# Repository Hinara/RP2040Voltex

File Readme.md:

# RP2040Voltex

Work in progress !! The PCB nor the schematics have been tested for now !! It is just a proof of concept !

It is a mini controller for games such as Sound Voltex, and clones.

This model is based on [Pocket-SDVX-Pico](https://github.com/speedypotato/Pocket-SDVX-Pico-v4)
The Lower PCB should be compatible [Pocket-SDVX-Pico](https://github.com/speedypotato/Pocket-SDVX-Pico-v4)

It's main difference is using directly a RP2040 processor to be able to meet the height constraints on the upper face. This was designed like that to prevent ripping of some Pico's component while putting the Pocket SDVX Pico in a bag without a case.

## Firmware

For now the firmware as not been updated to math the RP2040 pin layout, but you should be able to have a working firmware by compiling the [Pocket-SDVX-Pico](https://github.com/speedypotato/Pico-Game-Controller) firmware and change the pin layout.

## License

As it is derived work from [Pocket-SDVX-Pico](https://github.com/speedypotato/Pocket-SDVX-Pico-v4) it inherits the same [license](https://github.com/speedypotato/Pocket-SDVX-Pico-v4/blob/main/LICENSE).

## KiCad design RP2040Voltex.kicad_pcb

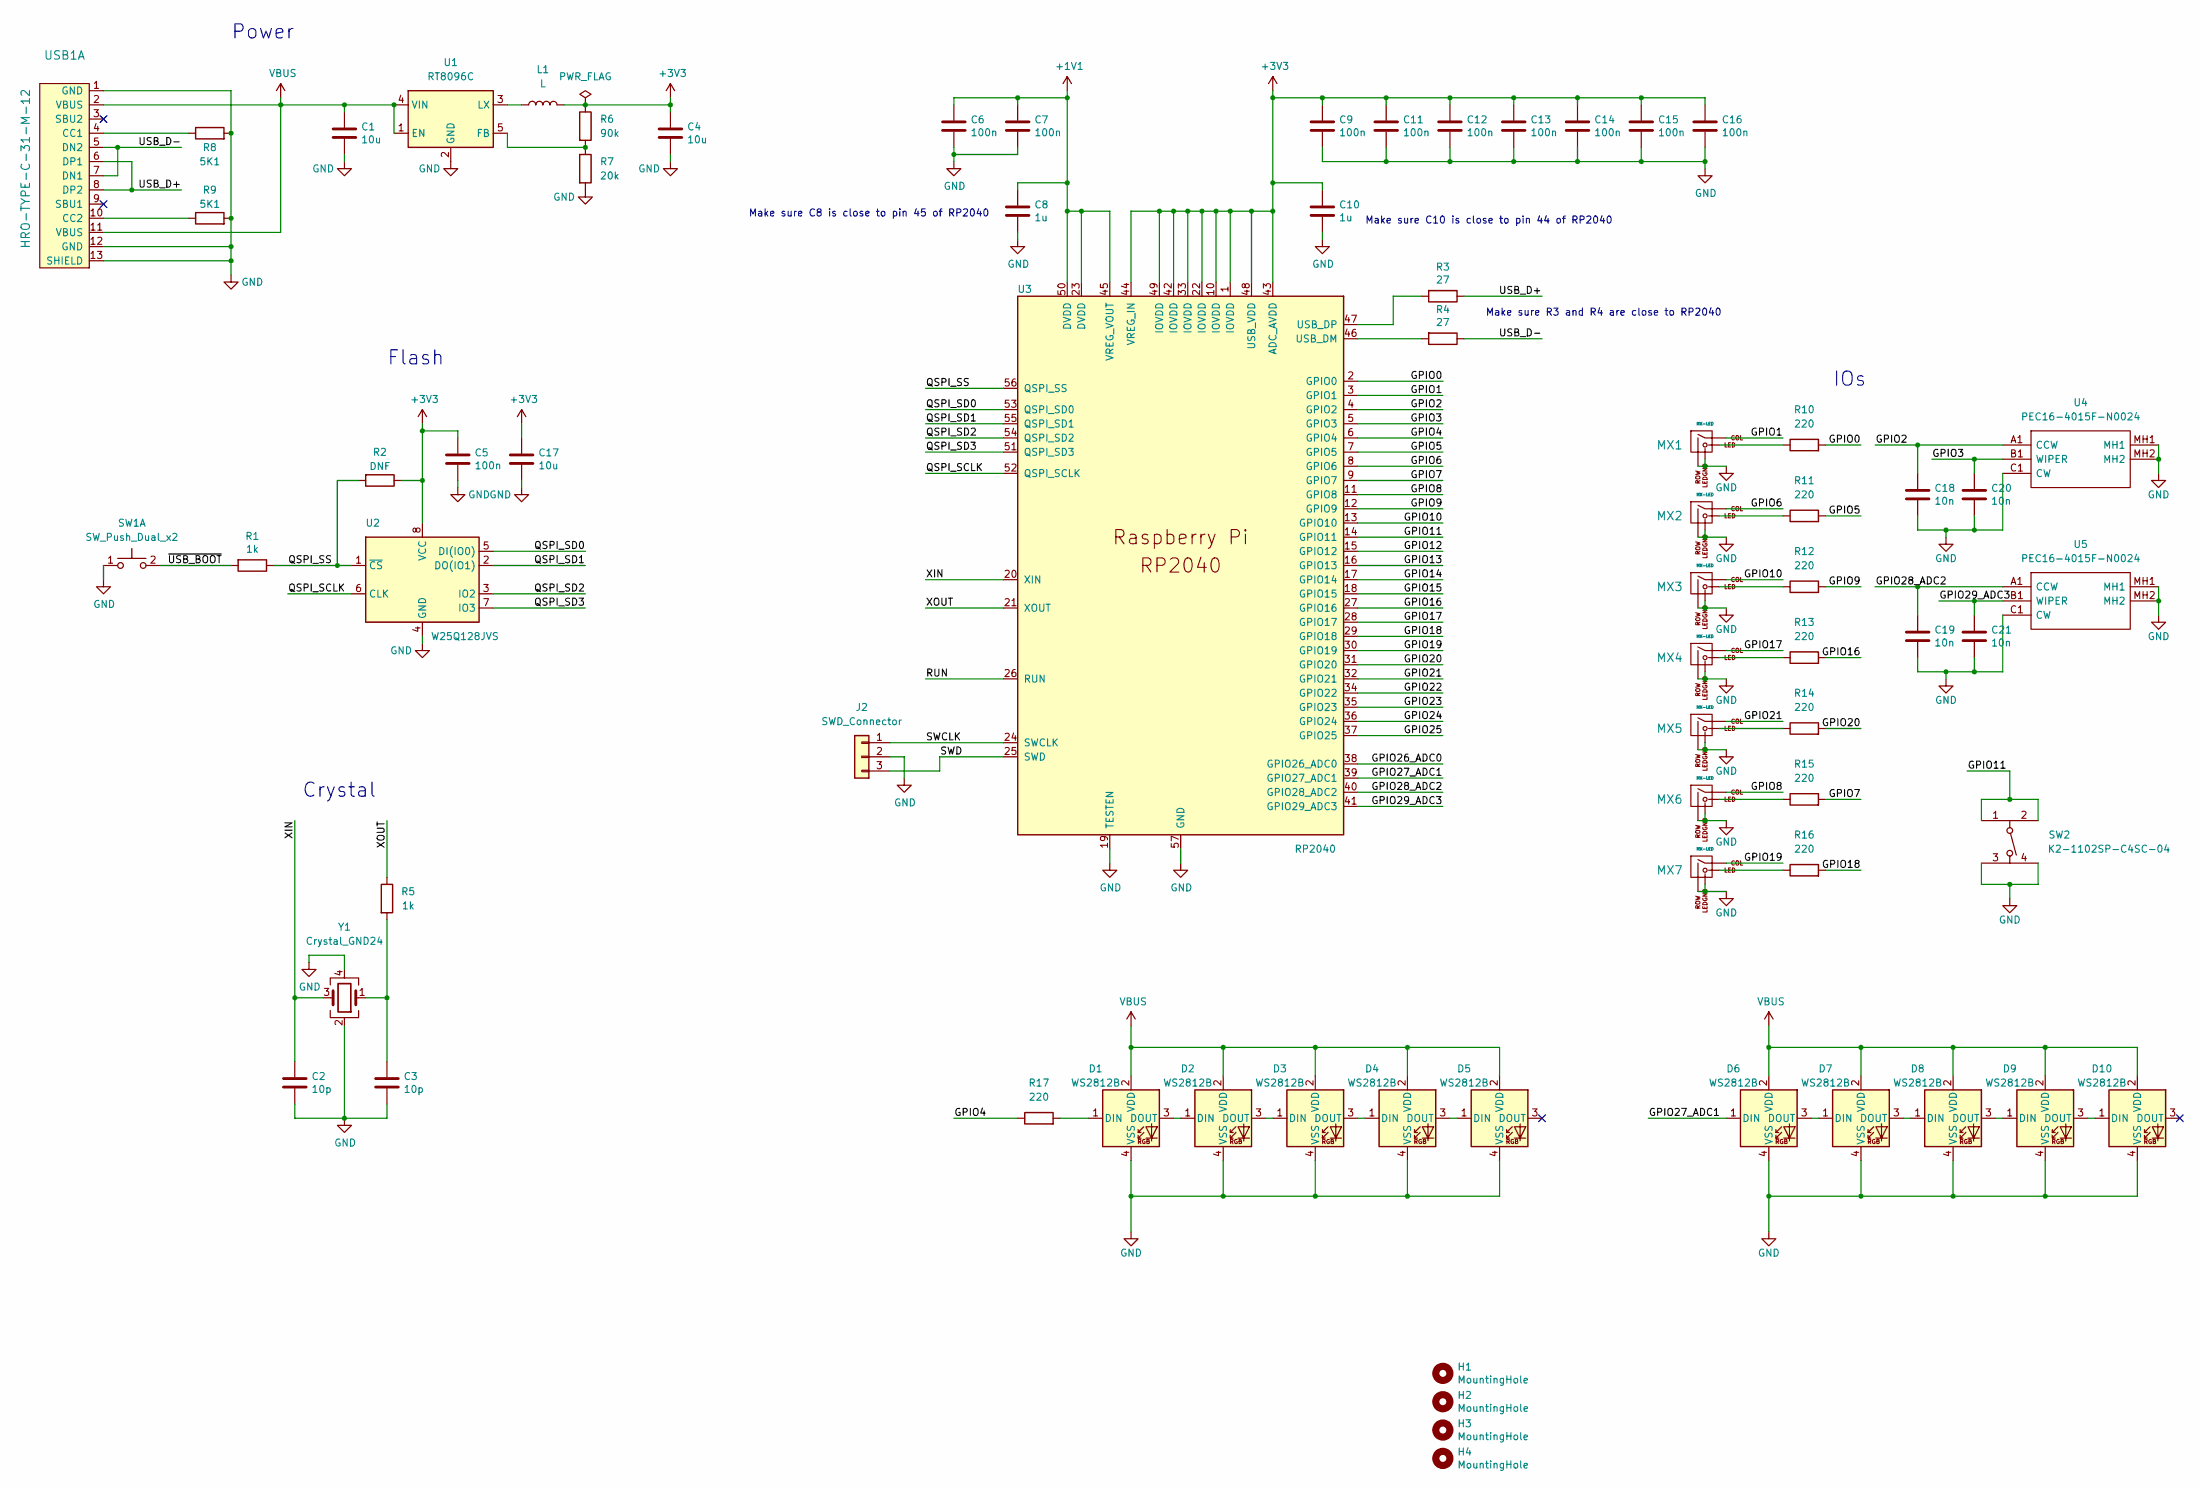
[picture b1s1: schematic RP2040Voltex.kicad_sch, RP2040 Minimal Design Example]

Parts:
C1: 10u; L_1008_2520Metric
C2, C3: 10p; C_0402_1005Metric
C4, C17: 10u; C_0805_2012Metric
C5, C6, C7, C9, C11, C12, C13, C14, C15, C16: 100n; C_0402_1005Metric
C8, C10: 1u; C_0402_1005Metric
C18, C19, C20, C21: 10n; C_0603_1608Metric
D1, D2, D3, D4, D5, D6, D7, D8, D9, D10: WS2812B; WS2812B-4020
H1, H2, H3, H4: MountingHole; MountingHole_3.2mm_M3
J2: SWD_Connector
L1: L; L_1008_2520Metric
MX1, MX2, MX3, MX4, MX5, MX6, MX7: MX-LED; MXOnly-1.5U-Hotswap-LED-SMD
R1, R5: 1k; R_0402_1005Metric
R2: DNF; R_0402_1005Metric
R3, R4: 27; R_0402_1005Metric
R6: 90k; R_0402_1005Metric
R7: 20k; R_0402_1005Metric
R8, R9: 5K1; R_0603_1608Metric
R10, R11, R12, R13, R14, R15, R16, R17: 220; R_0603_1608Metric
SW1: SW_Push_Dual_x2; TS-1012A
SW2: K2-1102SP-C4SC-04; KAN4542-0701C
U1: RT8096C; TSOT-23-5
U2: W25Q128JVS; SOIC-8_5.23x5.23mm_P1.27mm
U3: RP2040; RP2040-QFN-56
U4, U5: PEC16-4015F-N0024; PEC16-4015F-N0024-millmax; Mouser Part Number 652-PEC16-4015FN0024
USB1: HRO-TYPE-C-31-M-12; HRO-TYPE-C-31-M-12-Assembly
Y1: Crystal_GND24; Crystal_SMD_2520-4Pin_2.5x2.0mm

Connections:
+1V1: C6.1, C7.1, C8.1, U3.23 (DVDD), U3.45 (VREG_VOUT), U3.50 (DVDD)
+3V3: C4.1, C5.1, C9.1, C10.1, C11.1, C12.1, C13.1, C14.1, C15.1, C16.1, C17.1, L1.2, R2.1, R6.1, U2.8 (VCC), U3.1 (IOVDD), U3.10 (IOVDD), U3.22 (IOVDD), U3.33 (IOVDD), U3.42 (IOVDD), U3.43 (ADC_AVDD), U3.44 (VREG_IN), U3.48 (USB_VDD), U3.49 (IOVDD)
/GPIO0: R10.2, U3.2 (GPIO0)
/GPIO1: MX1.1 (COL), U3.3 (GPIO1)
/GPIO2: C18.1, U3.4 (GPIO2), U4.A1 (CCW)
/GPIO3: C20.1, U3.5 (GPIO3), U4.B1 (WIPER)
/GPIO4: R17.1, U3.6 (GPIO4)
/GPIO5: R11.2, U3.7 (GPIO5)
/GPIO6: MX2.1 (COL), U3.8 (GPIO6)
/GPIO7: R15.2, U3.9 (GPIO7)
/GPIO8: MX6.1 (COL), U3.11 (GPIO8)
/GPIO9: R12.2, U3.12 (GPIO9)
/GPIO10: MX3.1 (COL), U3.13 (GPIO10)
/GPIO11: SW2.1, SW2.2, U3.14 (GPIO11)
/GPIO12: U3.15 (GPIO12)
/GPIO13: U3.16 (GPIO13)
/GPIO14: U3.17 (GPIO14)
/GPIO15: U3.18 (GPIO15)
/GPIO16: R13.2, U3.27 (GPIO16)
/GPIO17: MX4.1 (COL), U3.28 (GPIO17)
/GPIO18: R16.2, U3.29 (GPIO18)
/GPIO19: MX7.1 (COL), U3.30 (GPIO19)
/GPIO20: R14.2, U3.31 (GPIO20)
/GPIO21: MX5.1 (COL), U3.32 (GPIO21)
/GPIO22: U3.34 (GPIO22)
/GPIO23: U3.35 (GPIO23)
/GPIO24: U3.36 (GPIO24)
/GPIO25: U3.37 (GPIO25)
/GPIO26_ADC0: U3.38 (GPIO26_ADC0)
/GPIO27_ADC1: D6.1 (DIN), U3.39 (GPIO27_ADC1)
/GPIO28_ADC2: C19.1, U3.40 (GPIO28_ADC2), U5.A1 (CCW)
/GPIO29_ADC3: C21.1, U3.41 (GPIO29_ADC3), U5.B1 (WIPER)
/QSPI_SCLK: U2.6 (CLK), U3.52 (QSPI_SCLK)
/QSPI_SD0: U2.5 (DI(IO0)), U3.53 (QSPI_SD0)
/QSPI_SD1: U2.2 (DO(IO1)), U3.55 (QSPI_SD1)
/QSPI_SD2: U2.3 (IO2), U3.54 (QSPI_SD2)
/QSPI_SD3: U2.7 (IO3), U3.51 (QSPI_SD3)
/QSPI_SS: R1.1, R2.2, U2.1 (~CS), U3.56 (QSPI_SS)
/RUN: U3.26 (RUN)
/SWCLK: J2.1 (SWCLK), U3.24 (SWCLK)
/SWD: J2.3 (SWDIO), U3.25 (SWD)
/USB_D+: R3.1, USB1.6 (DP1), USB1.8 (DP2)
/USB_D-: R4.1, USB1.5 (DN2), USB1.7 (DN1)
/XIN: C2.1, U3.20 (XIN), Y1.3
/XOUT: R5.1, U3.21 (XOUT)
/~USB_BOOT: R1.2, SW1.2 (D)
unnamed: C3.1, R5.2, Y1.1
unnamed: D1.1 (DIN), R17.2
unnamed: D1.3 (DOUT), D2.1 (DIN)
unnamed: D2.3 (DOUT), D3.1 (DIN)
unnamed: D3.3 (DOUT), D4.1 (DIN)
unnamed: D4.3 (DOUT), D5.1 (DIN)
unnamed: D6.3 (DOUT), D7.1 (DIN)
unnamed: D7.3 (DOUT), D8.1 (DIN)
unnamed: D8.3 (DOUT), D9.1 (DIN)
unnamed: D9.3 (DOUT), D10.1 (DIN)
unnamed: L1.1, U1.3 (LX)
unnamed: MX1.3 (LED), R10.1
unnamed: MX2.3 (LED), R11.1
unnamed: MX3.3 (LED), R12.1
unnamed: MX4.3 (LED), R13.1
unnamed: MX5.3 (LED), R14.1
unnamed: MX6.3 (LED), R15.1
unnamed: MX7.3 (LED), R16.1
unnamed: R3.2, U3.47 (USB_DP)
unnamed: R4.2, U3.46 (USB_DM)
unnamed: R6.2, R7.1, U1.5 (FB)
unnamed: R8.1, USB1.4 (CC1)
unnamed: R9.1, USB1.10 (CC2)

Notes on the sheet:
Make sure C10 is close to pin 44 of RP2040
Make sure C8 is close to pin 45 of RP2040
Crystal
Make sure R3 and R4 are close to RP2040
Flash
Power
IOs

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
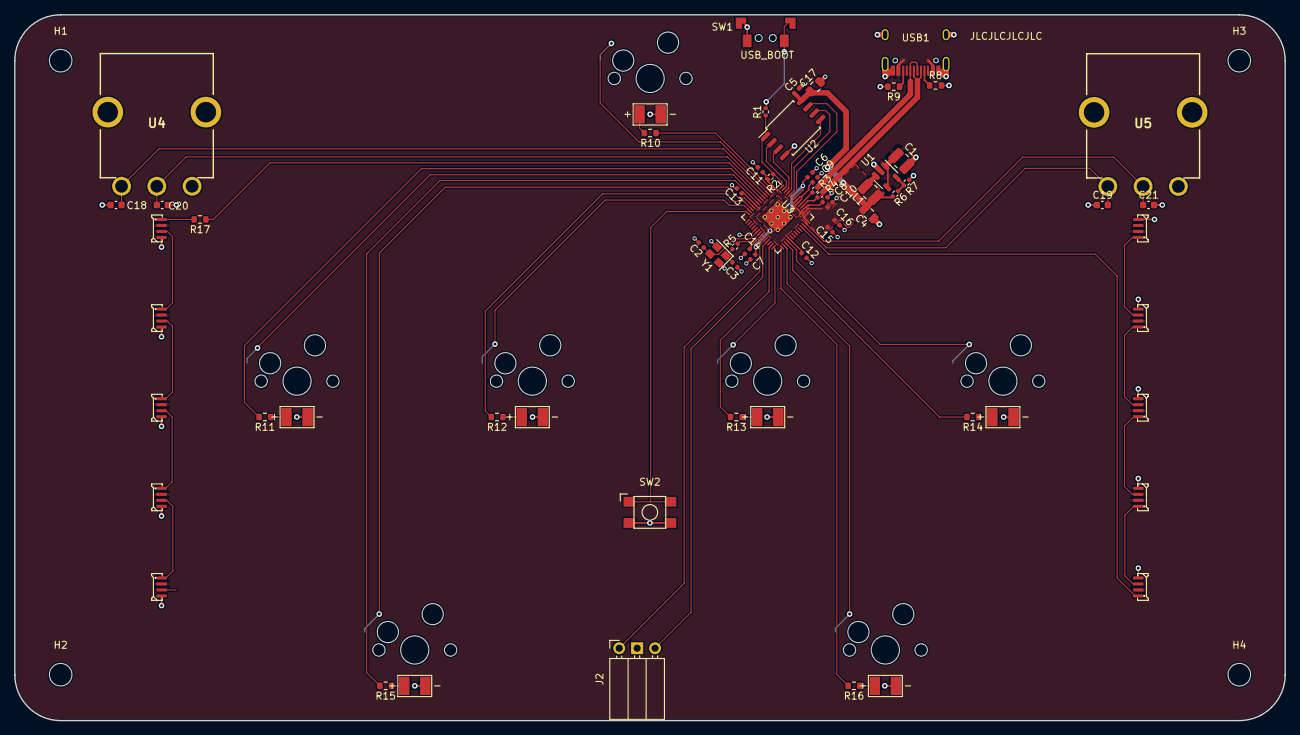
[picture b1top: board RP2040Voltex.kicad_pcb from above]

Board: 2 copper layers, 180.0 x 100.0 mm, 70 parts (0 on the bottom side), 61 nets.

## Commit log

2022-05-15 First Version of RP2040Voltex
2022-05-15 Make capacitor closer to encoders
2022-05-15 Change front plane to be power plane
2022-05-15 Split led strips + Put usb boot underneath
